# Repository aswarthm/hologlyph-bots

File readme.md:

desmos link https://www.desmos.com/calculator/cb8ouqfvlw

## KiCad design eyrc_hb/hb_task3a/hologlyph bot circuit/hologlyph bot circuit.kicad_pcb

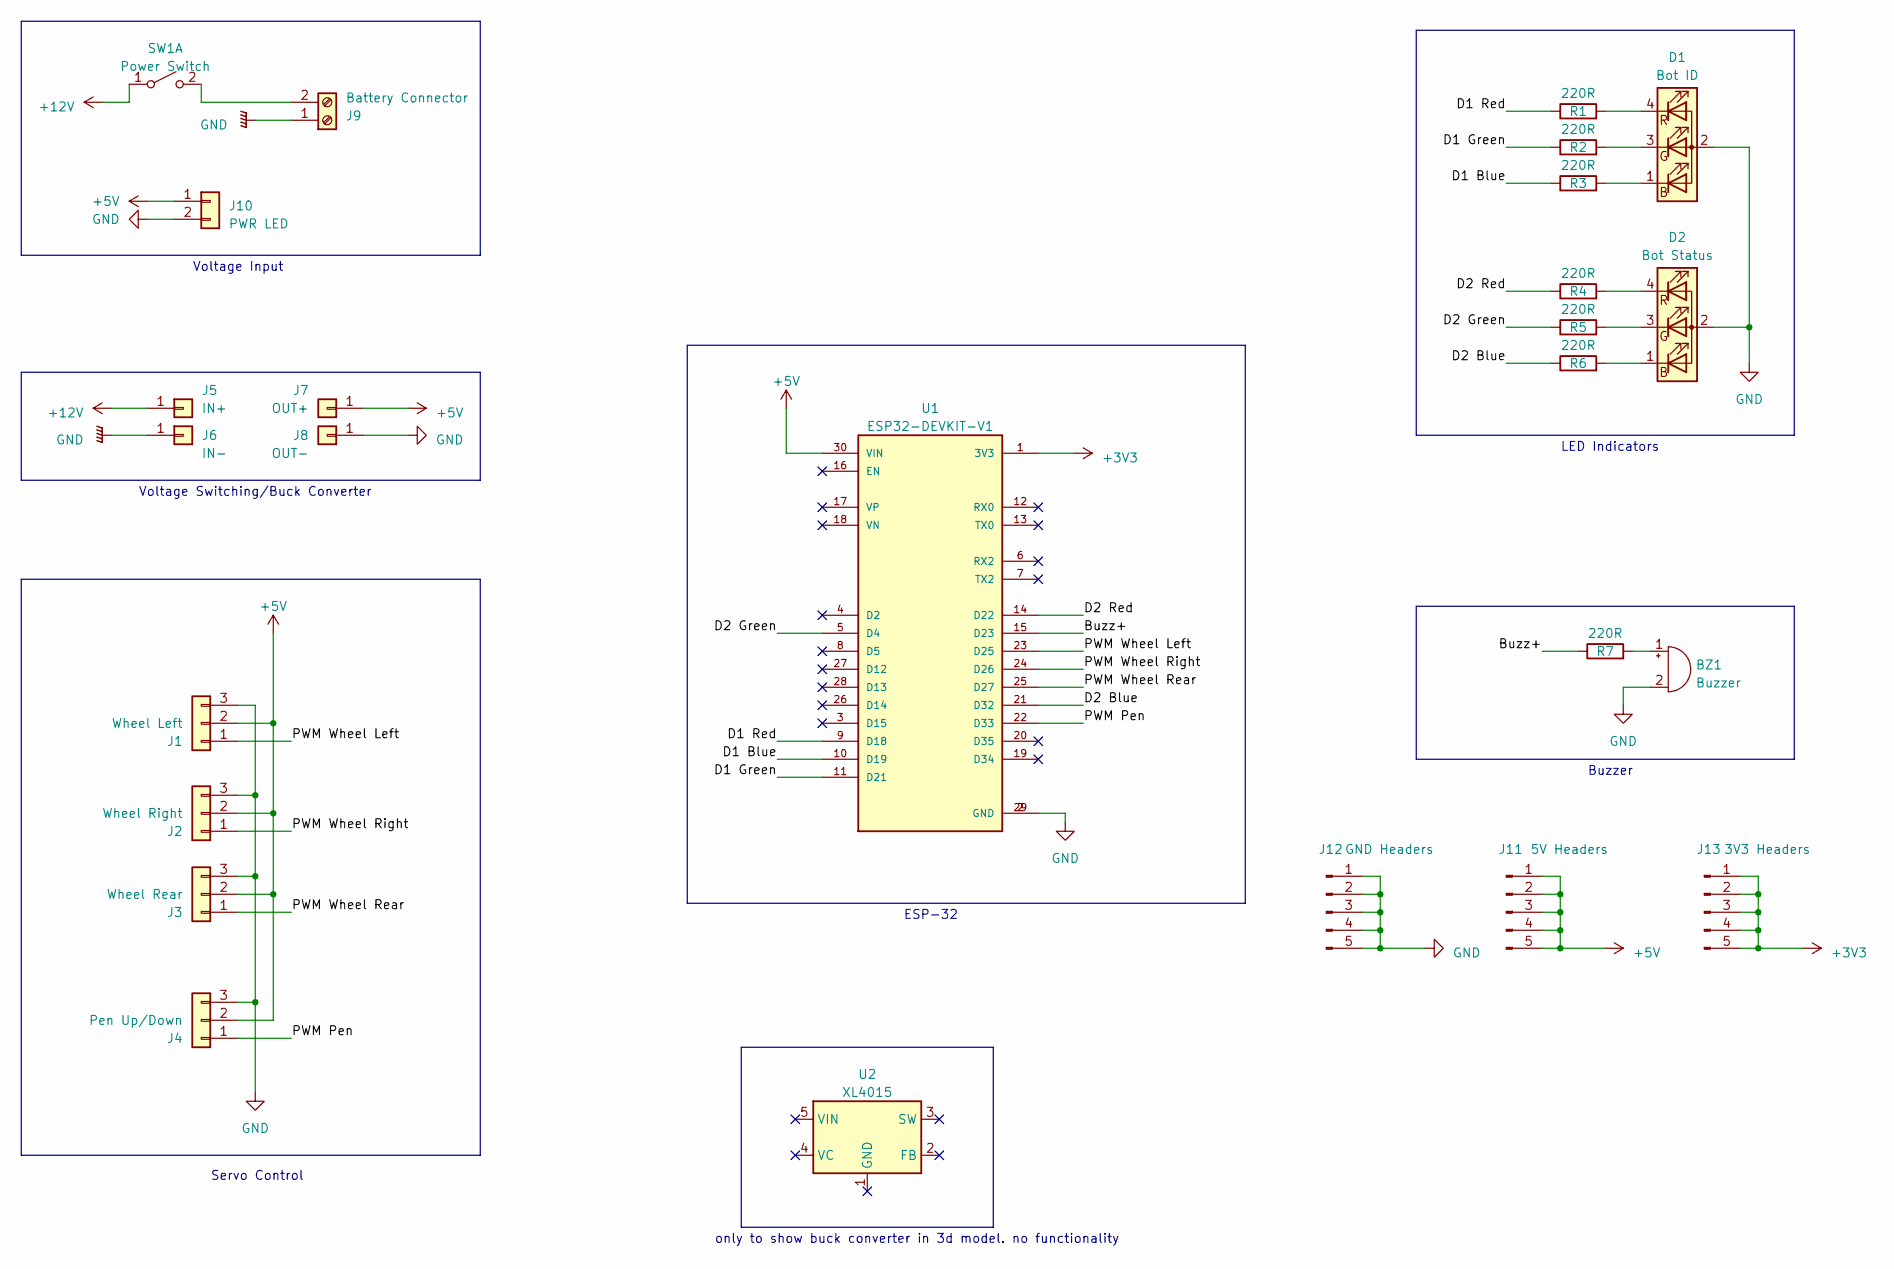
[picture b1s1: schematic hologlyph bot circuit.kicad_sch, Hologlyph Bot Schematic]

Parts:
BZ1: Buzzer; Buzzer_12x9.5RM7.6
D1: Bot ID; PinSocket_1x04_P2.54mm_Vertical
D2: Bot Status; PinSocket_1x04_P2.54mm_Vertical
J1: Wheel Left; PinHeader_1x03_P2.54mm_Vertical
J2: Wheel Right; PinHeader_1x03_P2.54mm_Vertical
J3: Wheel Rear; PinHeader_1x03_P2.54mm_Vertical
J4: Pen Up/Down; PinHeader_1x03_P2.54mm_Vertical
J5: IN+; PinHeader_1x01_P2.54mm_Vertical
J6: IN-; PinHeader_1x01_P2.54mm_Vertical
J7: OUT+; PinHeader_1x01_P2.54mm_Vertical
J8: OUT-; PinHeader_1x01_P2.54mm_Vertical
J9: Battery Connector; TerminalBlock_Altech_AK300-2_P5.00mm
J10: PWR LED; PinHeader_1x02_P2.54mm_Vertical
J11: 5V Headers; PinHeader_1x05_P2.54mm_Vertical
J12: GND Headers; PinHeader_1x05_P2.54mm_Vertical
J13: 3V3 Headers; PinHeader_1x05_P2.54mm_Vertical
R1, R2, R3, R4, R5, R6, R7: 220R; R_Axial_DIN0207_L6.3mm_D2.5mm_P7.62mm_Horizontal
SW1: Power Switch; PinHeader_1x02_P2.54mm_Vertical
U1: ESP32-DEVKIT-V1; MODULE_ESP32_DEVKIT_V1; PARTREV N/A
U2: XL4015; TO-263-5_TabPin3

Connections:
+3V3: J13.1, J13.2, J13.3, J13.4, J13.5, U1.1 (3V3); also elsewhere on the board
+5V: J1.2, J2.2, J3.2, J4.2, J7.1, J10.1, J11.1, J11.2, J11.3, J11.4, J11.5, U1.30 (VIN)
+12V: J5.1, SW1.1 (A)
/Buzz+: R7.1, U1.15 (D23)
/D1 Blue: R3.1, U1.10 (D19)
/D1 Green: R2.1, U1.11 (D21)
/D1 Red: R1.1, U1.9 (D18)
/D2 Blue: R6.1, U1.21 (D32)
/D2 Green: R5.1, U1.5 (D4)
/D2 Red: R4.1, U1.14 (D22)
/PWM Pen: J4.1, U1.22 (D33)
/PWM Wheel Left: J1.1, U1.23 (D25)
/PWM Wheel Rear: J3.1, U1.25 (D27)
/PWM Wheel Right: J2.1, U1.24 (D26)
unnamed: BZ1.1 (-), R7.2
unnamed: D1.1 (BK), R3.2
unnamed: D1.3 (GK), R2.2
unnamed: D1.4 (RK), R1.2
unnamed: D2.1 (BK), R6.2
unnamed: D2.3 (GK), R5.2
unnamed: D2.4 (RK), R4.2
unnamed: J9.2, SW1.2 (B)

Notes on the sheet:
only to show buck converter in 3d model. no functionality
Voltage Input
LED Indicators
Voltage Switching/Buck Converter
ESP-32
Buzzer
Servo Control

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
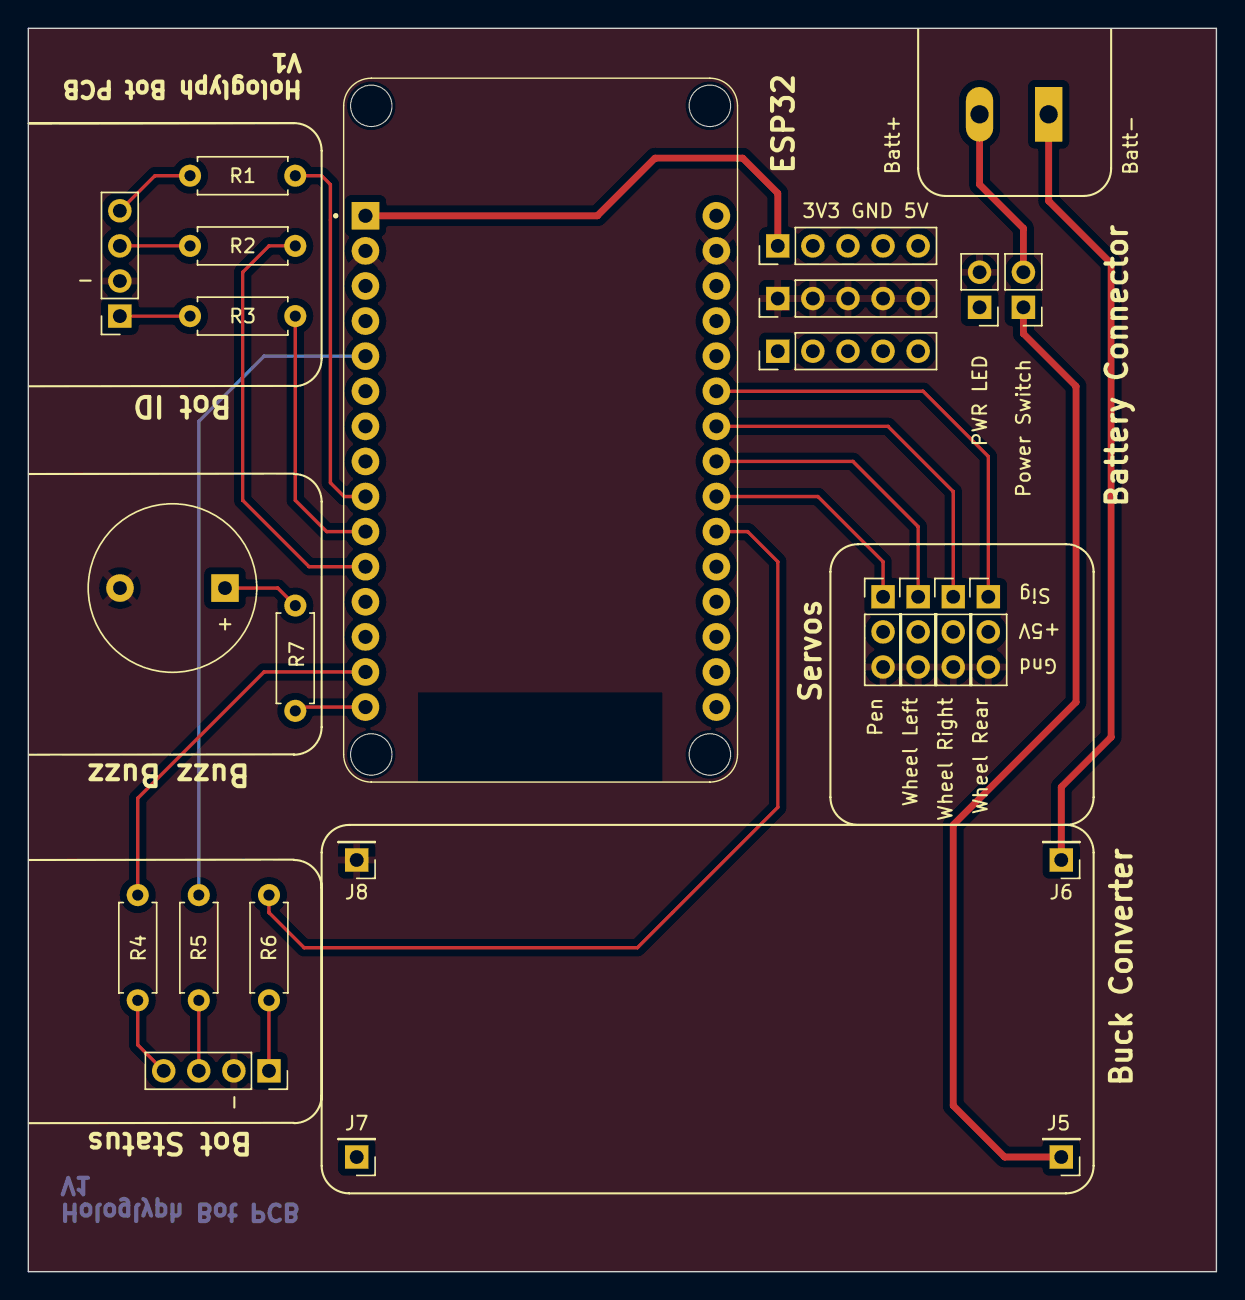
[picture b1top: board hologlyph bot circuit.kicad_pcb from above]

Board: 2 copper layers, 86.0 x 90.0 mm, 26 parts (0 on the bottom side), 24 nets.

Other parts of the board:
3V3 GND 5V: 3V3 Headers; PinHeader_1x05_P2.54mm_Vertical

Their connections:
+3V3: 3V3 GND 5V.1, 3V3 GND 5V.2, 3V3 GND 5V.3, 3V3 GND 5V.4, 3V3 GND 5V.5; also elsewhere on the board

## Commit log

2023-10-12 added git ignore
2023-10-12 edit gitignore
2023-10-12 fix gitignore
2023-10-12 [ImgBot] Optimize images
    *Total -- 695.39kb -> 544.39kb (21.71%)
    /eyrc_hb/hb_task1a_ws/submission/hb_task_1a_1036.png -- 536.22kb -> 417.09kb (22.22%)
    /zips/base_file/eyantra_logo.png -- 53.06kb -> 42.43kb (20.02%)
    /zips/Task_1B/meshes/17eyantra_logo_large e.png -- 53.06kb -> 42.43kb (20.02%)
    /eyrc_hb/hb_task1b_ws/src/hb_task_1b/meshes/eyantra_logo.png -- 53.06kb -> 42.43kb (20.02%)
2023-10-20 add task2 files
2023-10-20 get corners of aruco tags
2023-10-21 calibrate center based on corner aruco tags
2023-10-21 modify startup script
2023-10-22 optimise angle detection
2023-10-23 call next goal service and test wrench
2023-10-24 fix rotation matrix
2023-10-24 improve aruco detection
2023-10-24 added rotation matrix, and conversions from aruco to gazebo coordinates
2023-10-27 ik works
2023-10-28 plot path of bot on image
2023-10-28 cleanup unused code and add comments
2023-10-29 complete function comments
2023-10-30 task2a files + minor changes to check if score improves
2023-11-01 tried to change top left to 0,0
2023-11-01 task2a complete
2023-11-02 task2b setup
2023-11-09 task2b
2023-11-11 multi threaded controller instead of separate files for each bot
2023-11-11 task2b documentation/comments
2023-11-28 pcb layout done
2023-12-02 pcb circuit
2023-12-02 add hardware testing zip
2023-12-08 cam testing
2023-12-09 restructure folders and arena images
2023-12-09 3b and 3c done
2023-12-13 3d model and pcb
2023-12-20 model and pcb changes
2024-01-02 task4
2024-01-02 add pics
2024-01-02 remove calib images
2024-01-02 clean up code
2024-01-03 add motor constants
2024-01-11 reduce velocity topics
2024-01-13 add power headers
2024-01-18 combine feedback and controller
2024-01-28 function mode in sim
2024-01-28 improve angle control and destroy node at end of run and separate node for calling stop service
2024-01-29 changes to make it work with hardware
2024-01-30 arduino pen down
2024-01-30 fix angle
2024-01-31 hardware almost done
2024-02-07 task5b
2024-02-07 pcb minor changes
2024-02-07 5b vide
2024-02-15 collision checker
2024-02-19 cleanup collision checking and change goals to 2d array
2024-02-25 task6a
2024-02-25 Bharath Code
2024-02-25 Bharath change
2024-02-25 micro ros
2024-02-25 wait only for first 1 indices
2024-02-26 task 6b
2024-02-26 6a 6b pics
2024-02-26 Added comments
2024-02-27 grader files
2024-02-27 Arduino comments
2024-02-27 cleanup comments
2024-02-27 final submission
2024-02-27 compress images
2024-03-27 Added points generation code
